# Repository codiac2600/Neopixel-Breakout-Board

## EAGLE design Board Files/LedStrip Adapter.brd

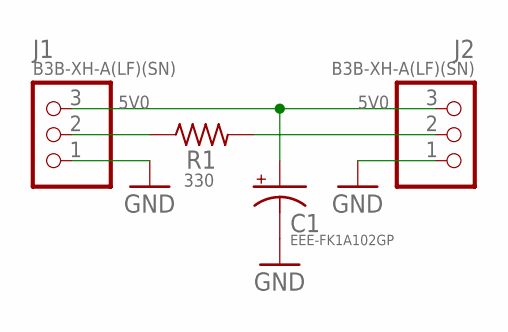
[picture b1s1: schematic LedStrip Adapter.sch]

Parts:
C1: EEE-FK1A102GP; PANASONIC_CAP_G
J1, J2: B3B-XH-A(LF)(SN)
R1: 330; 0603

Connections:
5V0: C1.POS (+), J1.3, J2.3
GND: C1.NEG (-), J1.1, J2.1
unnamed: J1.2, R1.1
unnamed: J2.2, R1.2

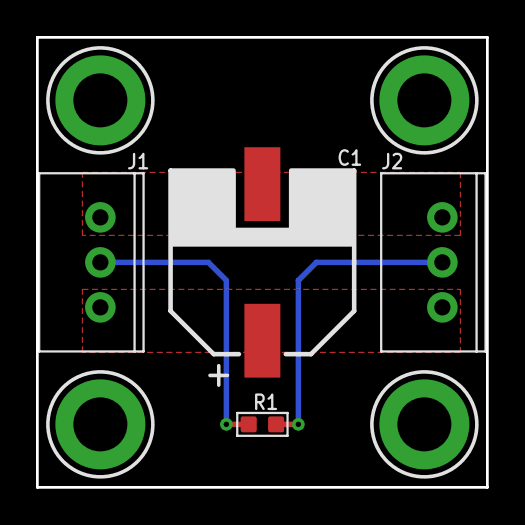
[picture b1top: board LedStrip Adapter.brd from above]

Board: 2 copper layers, 25.0 x 25.0 mm, 4 parts (0 on the bottom side), 4 nets.
